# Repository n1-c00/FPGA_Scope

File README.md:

# FPGA_Scope
In SMD-soldering there are a lot of very tiny parts with even smaller solder pads. If you really want to solder these parts, you need some sort of magnification. Commonly, a digital microscope is used here. The goal of this repo is to build something like this with as affordable as possible - specifically the CYC1000 from Trenz Electronics, and an OminVision OV5640 Camera.

## Hardware
As stated, the main Chip/DevKit is the Cyclone 10 LP from Altera on the CYC1000.
For this DevKit, I will be designing a daugtherboard which allows the connection of the OV5640 to the FPGA and also adds an HDMI-Port for streaming the Data to a Display.

## Software
For using the scope there will be two possible ways:
1. There is the obvious HDMI-Port poking out from the dautherboard. This will be a HDMI-Source that streams the videofeed to any monitor you'd like.
2. In Addition to this you can connect the FPGA via USB to your PC and run the python file in ./software in order to use it "on the fly". I also would like to add some machine vision features like part detections or
   component-marker-enhancement. This will preferably run on the FPGA or on your local PC. I can't really tell you since this is all WIP...

## Further Links
- [CYC1000 Wiki](https://wiki.trenz-electronic.de/display/PD/TEI0003+Resources)
- [LeFlow](https://github.com/danielholanda/LeFlow)
- [DearPyGUI](https://dearpygui.readthedocs.io/en/latest/)

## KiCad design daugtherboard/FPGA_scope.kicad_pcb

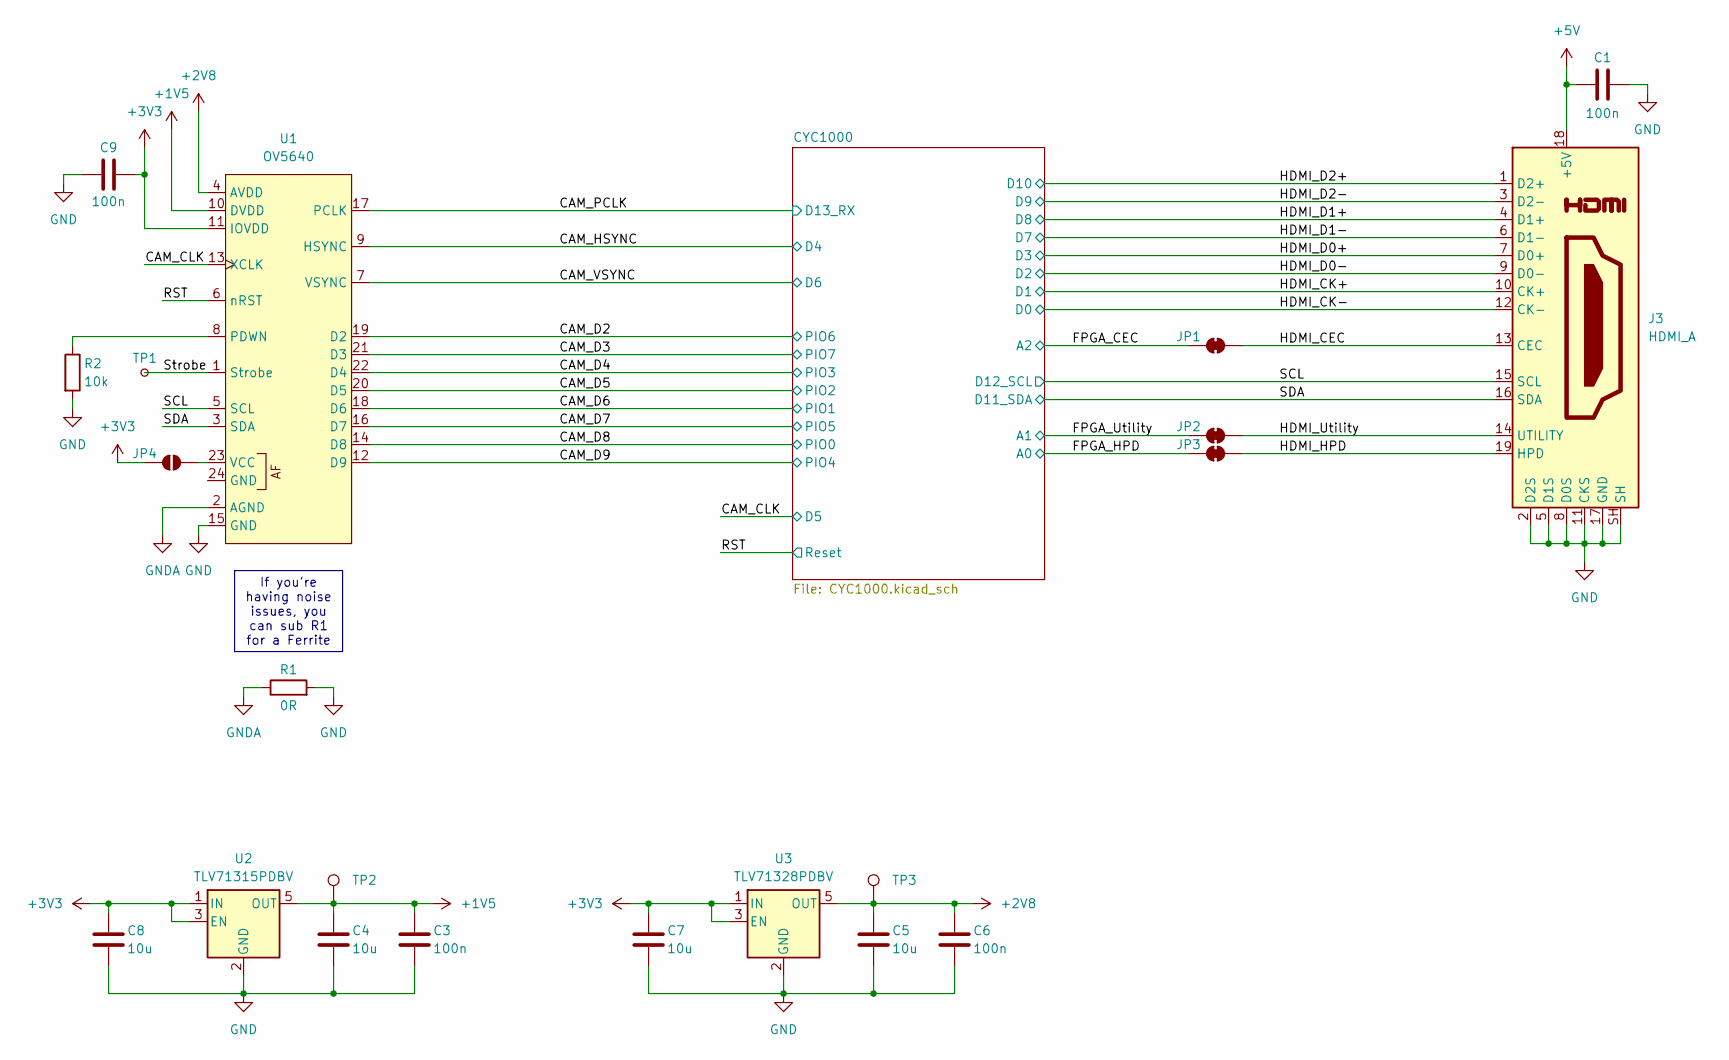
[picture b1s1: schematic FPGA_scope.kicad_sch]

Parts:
C1, C3, C6, C9: 100n; C_0805_2012Metric
C4, C5, C7, C8: 10u; C_0805_2012Metric
J3: HDMI_A; HDMI_A_Amphenol_10029449-x01xLF_Horizontal
JP1, JP2, JP3: SolderJumper_2_Bridged; SolderJumper-2_P1.3mm_Bridged_RoundedPad1.0x1.5mm
JP4: SolderJumper_2_Open; SolderJumper-2_P1.3mm_Open_RoundedPad1.0x1.5mm
R1: 0R; R_0805_2012Metric
R2: 10k; R_0805_2012Metric
TP1: TestPoint_Small; TestPoint_Pad_D1.5mm
TP2, TP3: TestPoint; TestPoint_Pad_D1.5mm
U1: OV5640; XYECONN_FPC02-S0.5-24AH2.0_24Pin_P0.5mm
U2: TLV71315PDBV; SOT-23-5
U3: TLV71328PDBV; SOT-23-5

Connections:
+1V5: C3.1, C4.1, TP2.1, U1.10 (DVDD), U2.5 (OUT)
+2V8: C5.1, C6.1, TP3.1, U1.4 (AVDD), U3.5 (OUT)
+3V3: C7.1, C8.1, C9.2, JP4.1 (A), U1.11 (IOVDD), U2.1 (IN), U2.3 (EN), U3.1 (IN), U3.3 (EN); also elsewhere on the board
+5V: C1.1, J3.18 (+5V); also elsewhere on the board
/CAM_CLK: U1.13 (XCLK); also elsewhere on the board
/CAM_D2: U1.19 (D2); also elsewhere on the board
/CAM_D3: U1.21 (D3); also elsewhere on the board
/CAM_D4: U1.22 (D4); also elsewhere on the board
/CAM_D5: U1.20 (D5); also elsewhere on the board
/CAM_D6: U1.18 (D6); also elsewhere on the board
/CAM_D7: U1.16 (D7); also elsewhere on the board
/CAM_D8: U1.14 (D8); also elsewhere on the board
/CAM_D9: U1.12 (D9); also elsewhere on the board
/CAM_HSYNC: U1.9 (HSYNC); also elsewhere on the board
/CAM_PCLK: U1.17 (PCLK); also elsewhere on the board
/CAM_VSYNC: U1.7 (VSYNC); also elsewhere on the board
/FPGA_CEC: JP1.1 (A); also elsewhere on the board
/FPGA_HPD: JP3.1 (A); also elsewhere on the board
/FPGA_Utility: JP2.1 (A); also elsewhere on the board
/HDMI_CEC: J3.13 (CEC), JP1.2 (B)
/HDMI_CK+: J3.10 (CK+); also elsewhere on the board
/HDMI_CK-: J3.12 (CK-); also elsewhere on the board
/HDMI_D0+: J3.7 (D0+); also elsewhere on the board
/HDMI_D0-: J3.9 (D0-); also elsewhere on the board
/HDMI_D1+: J3.4 (D1+); also elsewhere on the board
/HDMI_D1-: J3.6 (D1-); also elsewhere on the board
/HDMI_D2+: J3.1 (D2+); also elsewhere on the board
/HDMI_D2-: J3.3 (D2-); also elsewhere on the board
/HDMI_HPD: J3.19 (HPD), JP3.2 (B)
/HDMI_Utility: J3.14 (UTILITY), JP2.2 (B)
/RST: U1.6 (nRST); also elsewhere on the board
/SCL: J3.15 (SCL), U1.5 (SCL); also elsewhere on the board
/SDA: J3.16 (SDA), U1.3 (SDA); also elsewhere on the board
/Strobe: TP1.1, U1.1 (Strobe)
GND: C1.2, C3.2, C4.2, C5.2, C6.2, C7.2, C8.2, C9.1, J3.2 (D2S), J3.5 (D1S), J3.8 (D0S), J3.11 (CKS), J3.17 (GND), J3.SH, R1.2, R2.2, U1.15 (GND), U2.2 (GND), U3.2 (GND); also elsewhere on the board
GNDA: R1.1, U1.2 (AGND)
unnamed: JP4.2 (B), U1.23 (VCC)
unnamed: R2.1, U1.8 (PDWN)

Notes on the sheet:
If you're having noise issues, you can sub R1 for a Ferrite

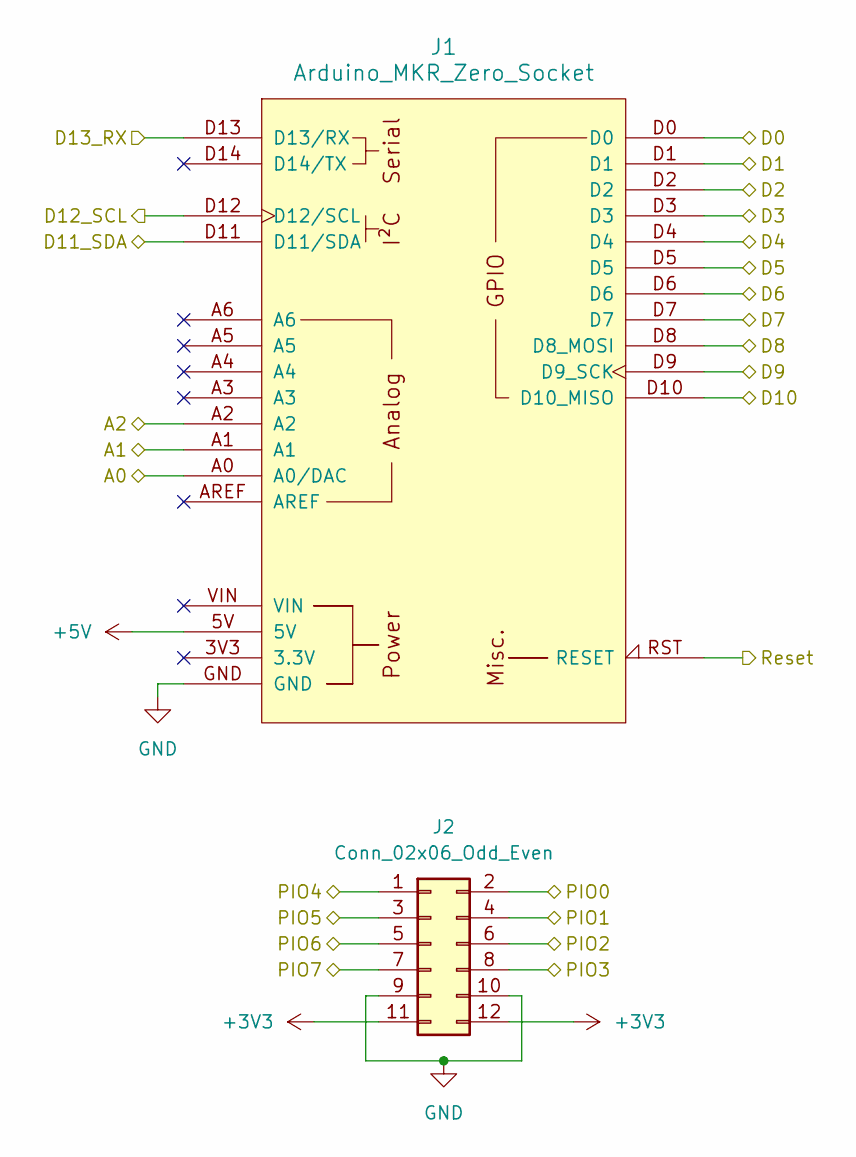
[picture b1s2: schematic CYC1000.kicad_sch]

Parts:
J1: Arduino_MKR_Zero_Socket
J2: Conn_02x06_Odd_Even; PinSocket_2x06_P2.54mm_Vertical

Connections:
+3V3: J2.11, J2.12; also elsewhere on the board
+5V: J1.5V; also elsewhere on the board
/CAM_CLK: J1.D5; also elsewhere on the board
/CAM_D2: J2.5; also elsewhere on the board
/CAM_D3: J2.7; also elsewhere on the board
/CAM_D4: J2.8; also elsewhere on the board
/CAM_D5: J2.6; also elsewhere on the board
/CAM_D6: J2.4; also elsewhere on the board
/CAM_D7: J2.3; also elsewhere on the board
/CAM_D8: J2.2; also elsewhere on the board
/CAM_D9: J2.1; also elsewhere on the board
/CAM_HSYNC: J1.D4; also elsewhere on the board
/CAM_PCLK: J1.D13 (D13/RX); also elsewhere on the board
/CAM_VSYNC: J1.D6; also elsewhere on the board
/FPGA_CEC: J1.A2; also elsewhere on the board
/FPGA_HPD: J1.A0 (A0/DAC); also elsewhere on the board
/FPGA_Utility: J1.A1; also elsewhere on the board
/HDMI_CK+: J1.D1; also elsewhere on the board
/HDMI_CK-: J1.D0; also elsewhere on the board
/HDMI_D0+: J1.D3; also elsewhere on the board
/HDMI_D0-: J1.D2; also elsewhere on the board
/HDMI_D1+: J1.D8 (D8_MOSI); also elsewhere on the board
/HDMI_D1-: J1.D7; also elsewhere on the board
/HDMI_D2+: J1.D10 (D10_MISO); also elsewhere on the board
/HDMI_D2-: J1.D9 (D9_SCK); also elsewhere on the board
/RST: J1.RST (RESET); also elsewhere on the board
/SCL: J1.D12 (D12/SCL); also elsewhere on the board
/SDA: J1.D11 (D11/SDA); also elsewhere on the board
GND: J1.GND, J2.9, J2.10; also elsewhere on the board

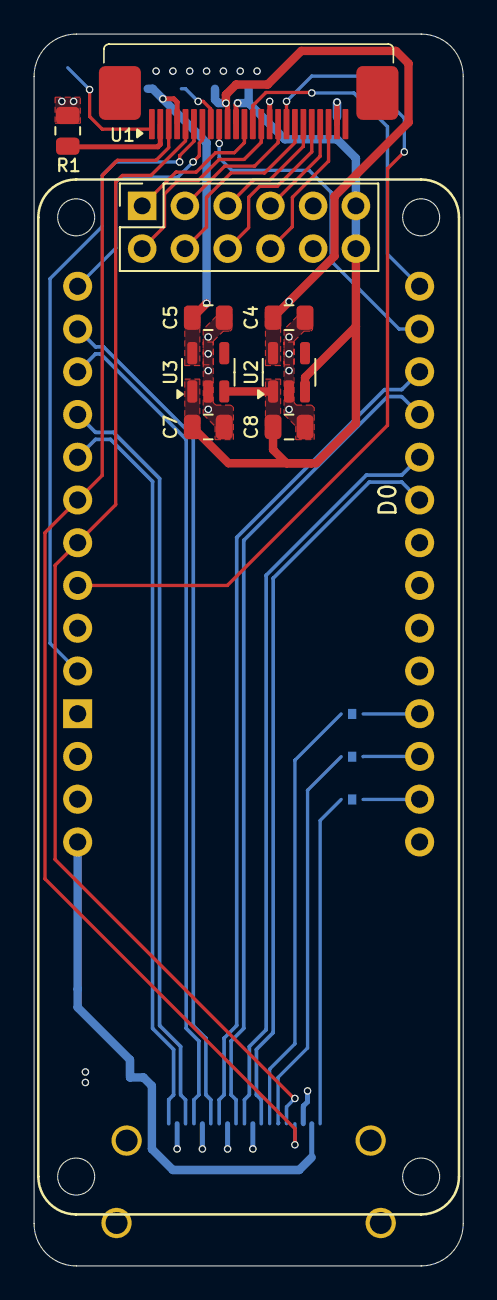
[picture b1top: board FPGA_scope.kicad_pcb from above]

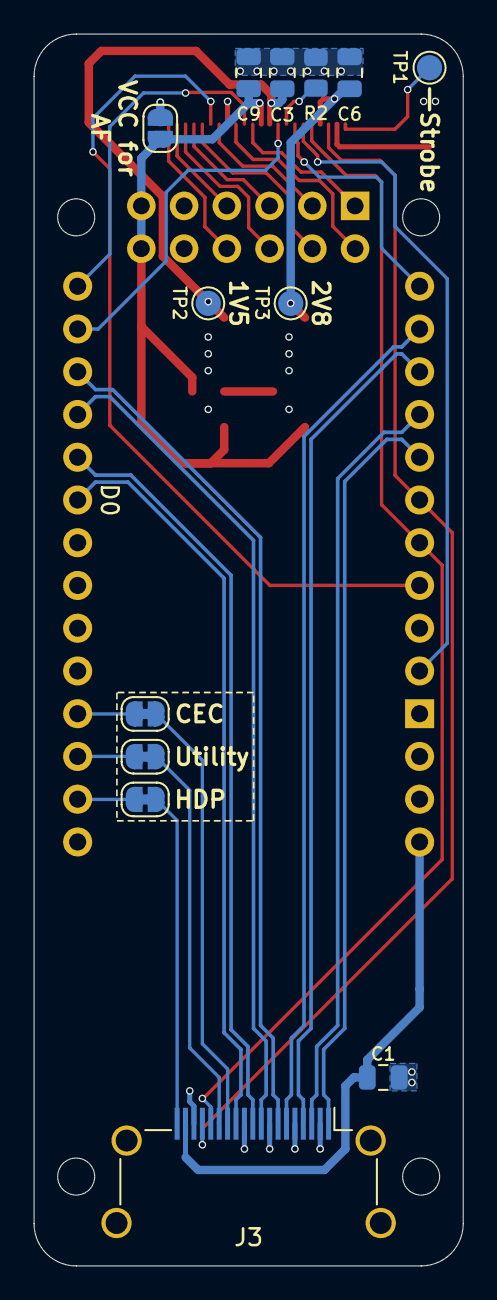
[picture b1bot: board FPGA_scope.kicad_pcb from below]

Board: 4 copper layers, 25.5 x 73.2 mm, 23 parts (13 on the bottom side), 38 nets.

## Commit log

2026-01-03 First Drawup of Schematic and PCB
2026-01-08 start of PC Software
2026-01-10 Tested GUI-framework with cv2 video-stream
2026-01-10 added requirements.txt
